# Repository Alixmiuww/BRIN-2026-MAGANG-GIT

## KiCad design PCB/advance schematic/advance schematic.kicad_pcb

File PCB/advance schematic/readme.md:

# ESP32 Controller — Schematic Documentation

## 1. Deskripsi Proyek

Proyek ini merupakan pengembangan rangkaian kontroler berbasis **ESP32-DevKitC-32E** yang menggunakan dua modul joystick analog, beberapa tombol kontrol, sensor GY-521 (MPU6050), LED RGB, serta rangkaian pemantauan tegangan baterai.

Rangkaian dirancang sebagai perangkat input untuk membaca pergerakan joystick, menerima perintah dari tombol, dan menyediakan data sensor untuk kebutuhan sistem kendali elektronik, seperti robot atau kendaraan berbasis mikrokontroler.

## 2. Fitur Utama

- **Dual Analog Joystick:** Membaca input sumbu X dan Y dari dua modul joystick.
- **Button Control:** Menyediakan tombol untuk kontrol drop, pickup, peningkatan kecepatan, penurunan kecepatan, dan pemilihan mode.
- **IMU Sensor:** Menggunakan GY-521 berbasis MPU6050 untuk membaca percepatan dan kecepatan sudut.
- **Battery Voltage Monitoring:** Menyediakan rangkaian pembagi tegangan untuk membaca tegangan baterai melalui ADC ESP32.
- **RGB LED Indicator:** Menyediakan indikator visual melalui LED RGB.
- **ESP32 Microcontroller:** Bertindak sebagai pusat pembacaan input dan pemrosesan data kontrol.

## 3. Komponen yang Digunakan

| Komponen | Fungsi |
|---|---|
| ESP32-DevKitC-32E | Mikrokontroler utama |
| 2× Joystick Module | Input analog sumbu X dan Y |
| 6× Push Button | Input perintah kontrol |
| GY-521 (MPU6050) | Sensor gerak berbasis IMU |
| LED RGB | Indikator status |
| Resistor 10 kΩ | Jaringan tombol dan pembagi tegangan |
| Resistor 100 kΩ | Pembagi tegangan pemantauan baterai |
| Konektor baterai | Input tegangan baterai |
| Sakelar | Pengendalian jalur rangkaian sesuai skematik |

## 4. Pemetaan Pin ESP32

### A. Input Joystick

| Sinyal | GPIO ESP32 |
|---|---:|
| JOY.VRx1 | GPIO 33 |
| JOY.VRy1 | GPIO 32 |
| JOY.VRx2 | GPIO 35 |
| JOY.VRy2 | GPIO 34 |

GPIO 32, 33, 34, dan 35 digunakan untuk membaca sinyal analog dari kedua joystick. GPIO 34 dan GPIO 35 merupakan pin input-only sehingga sesuai untuk pembacaan ADC.

### B. Tombol Kontrol

| Sinyal | GPIO ESP32 | Fungsi |
|---|---:|---|
| CONTROL.drop | GPIO 13 | Perintah drop |
| CONTROL.plck | GPIO 14 | Perintah pickup |
| CONTROL.up | GPIO 26 | Menaikkan kecepatan |
| CONTROL.down | GPIO 25 | Menurunkan kecepatan |
| SW.mode.joy1 | GPIO 18 | Pemilihan mode joystick |
| SW.mode.sensor | GPIO 19 | Pemilihan mode sensor |

**Catatan:** Pemetaan pin mengikuti label jaringan pada skematik. Pastikan konfigurasi pin pada program sesuai dengan hasil akhir desain PCB.

### C. Sensor GY-521 (MPU6050)

| Sinyal | Koneksi |
|---|---|
| VCC | +5 V sesuai skematik |
| GND | GND |
| SDA | Jalur I²C SDA |
| SCL | Jalur I²C SCL |
| AD0 | Tidak terhubung |
| INT | Tidak terhubung |
| XCL dan XDA | Tidak terhubung |

Jalur SDA dan SCL dihubungkan ke GPIO ESP32 yang ditentukan dalam konfigurasi perangkat lunak. Pin AD0 yang tidak terhubung umumnya membuat alamat I²C MPU6050 berada pada `0x68`, tetapi kondisi pin perlu dipastikan pada modul yang digunakan.

### D. LED RGB

LED RGB digunakan sebagai indikator status perangkat. Setiap kanal warna terhubung ke jalur GPIO melalui rangkaian pada skematik.

**Catatan:** Nomor GPIO untuk setiap kanal LED perlu dipastikan dari label net dan koneksi lengkap pada skematik sebelum diimplementasikan dalam kode.

### E. Pemantauan Tegangan Baterai

Rangkaian pemantauan tegangan menggunakan resistor pembagi tegangan untuk menyesuaikan tegangan baterai dengan rentang input ADC ESP32.

Nilai tegangan input dapat dihitung menggunakan:

`V_baterai = V_ADC × (R_atas + R_bawah) / R_bawah`

Rumus tersebut berlaku untuk pembagi tegangan standar, dengan `R_atas` terhubung dari baterai positif ke titik ADC dan `R_bawah` terhubung dari titik ADC ke GND.

**Penting:** Nilai resistor dan jalur pada skematik perlu diverifikasi. Pastikan tegangan yang masuk ke pin ADC tidak melebihi batas aman ESP32. Jika ingin mengukur tegangan baterai di atas rentang ADC, gunakan pembagi tegangan yang sesuai.

## 5. Prinsip Kerja Sistem

1. ESP32 dinyalakan melalui sumber daya yang sesuai.
2. Kedua joystick menghasilkan sinyal analog sesuai posisi sumbu X dan Y.
3. ESP32 membaca perubahan sinyal analog melalui ADC.
4. Tombol memberikan perintah digital untuk drop, pickup, pengaturan kecepatan, dan pemilihan mode.
5. Sensor MPU6050 menyediakan data percepatan dan kecepatan sudut melalui komunikasi I²C.
6. Rangkaian pembagi tegangan menyediakan sinyal yang mewakili tegangan baterai untuk dipantau ESP32.
7. Data input diproses oleh firmware untuk menentukan perintah kontrol dan status sistem.

## 6. Perangkat Lunak

Firmware dapat dikembangkan menggunakan Arduino IDE atau PlatformIO dengan framework Arduino.

Library yang dapat digunakan:
- `Arduino.h` — fungsi dasar ESP32.
- `Wire.h` — komunikasi I²C.
- Library MPU6050 yang kompatibel — pembacaan data IMU.

## 7. Catatan Desain dan Pengujian

Sebelum rangkaian diproduksi atau digunakan, lakukan pemeriksaan berikut:

- Verifikasi semua koneksi daya, GND, dan GPIO.
- Pastikan setiap tombol memiliki logika input yang sesuai dengan konfigurasi resistor.
- Periksa apakah resistor 10 kΩ pada jaringan tombol berfungsi sebagai pull-up atau pull-down sesuai kebutuhan.
- Pastikan tegangan keluaran joystick tidak melebihi batas ADC ESP32.
- Verifikasi konfigurasi pembagi tegangan baterai dan batas tegangan ADC.
- Pastikan LED RGB memiliki resistor pembatas arus yang sesuai untuk setiap kanal.
- Periksa alamat I²C MPU6050 dan jalur SDA/SCL menggunakan pemindaian I²C.
- Lakukan pemeriksaan ERC pada skematik dan DRC pada layout PCB sebelum fabrikasi.

## 8. Kesimpulan

Rangkaian ini dirancang sebagai kontroler berbasis ESP32 dengan input joystick analog, tombol digital, sensor IMU, indikator RGB, dan pemantauan tegangan baterai. Integrasi komponen tersebut memungkinkan ESP32 mengumpulkan berbagai input untuk diproses menjadi perintah kendali. Validasi koneksi daya, pemetaan GPIO, dan rangkaian ADC perlu dilakukan sebelum implementasi perangkat lunak dan pembuatan PCB.

## 9. Schematic Rancangan

## 10. PCB Rancangan

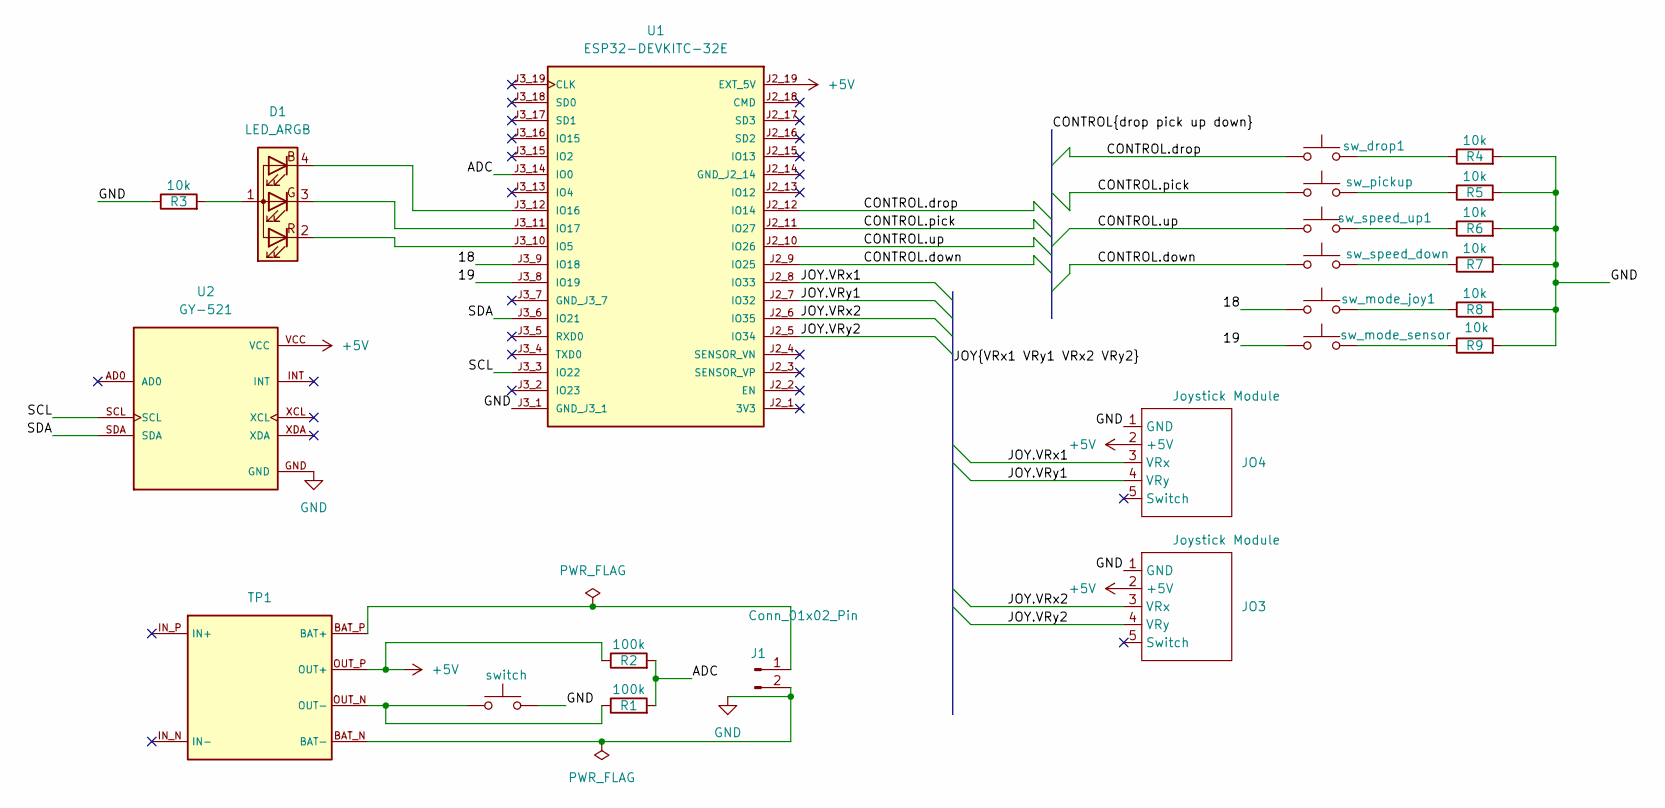
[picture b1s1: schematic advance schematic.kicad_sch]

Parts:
D1: LED_ARGB; LED_D5.0mm-4_RGB_Wide_Pins
J1: Conn_01x02_Pin; JST_EH_B2B-EH-A_1x02_P2.50mm_Vertical
JO3, JO4: Joystick Module; Module joystick
R1, R2: 100k; R_Axial_DIN0204_L3.6mm_D1.6mm_P1.90mm_Vertical
R3, R4, R5, R6, R7, R8, R9: 10k; R_Axial_DIN0204_L3.6mm_D1.6mm_P1.90mm_Vertical
SW2: sw_pickup; SW_PUSH_6mm
SW3: sw_speed_down; SW_PUSH_6mm
SW4: sw_mode_sensor; SW_PUSH_6mm
SW5: switch; SW_DIP_SPSTx01_Slide_6.7x4.1mm_W7.62mm_P2.54mm_LowProfile
TP1: MODULE_TP4056_MICRO-USB_CHARGER_-_1A
U1: ESP32-DEVKITC-32E; MODULE_ESP32-DEVKITC-32E; PARTREV 1.4
U2: GY-521; MODULE_GY-521; PARTREV NA
sw_drop1: SW_Push; SW_PUSH_6mm
sw_mode_joy1: SW_Push; SW_PUSH_6mm
sw_speed_up1: SW_Push; SW_PUSH_6mm

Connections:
+5V: JO3.2 (+5V), JO4.2 (+5V), R2.1, TP1.OUT_P (OUT+), U1.J2_19 (EXT_5V), U2.VCC
/18: U1.J3_9 (IO18), sw_mode_joy1.1
/19: SW4.1, U1.J3_8 (IO19)
/<NO NET>: D1.2 (RK), D1.4 (BK), U1.J3_10 (IO5), U1.J3_12 (IO16)
/ADC: R1.2, R2.2, U1.J3_14 (IO0)
/CONTROL.down: SW3.1, U1.J2_9 (IO25)
/CONTROL.drop: U1.J2_12 (IO14), sw_drop1.1
/CONTROL.pick: SW2.1, U1.J2_11 (IO27)
/CONTROL.up: U1.J2_10 (IO26), sw_speed_up1.1
/JOY.VRx1: JO4.3 (VRx), U1.J2_8 (IO33)
/JOY.VRx2: JO3.3 (VRx), U1.J2_6 (IO35)
/JOY.VRy1: JO4.4 (VRy), U1.J2_7 (IO32)
/JOY.VRy2: JO3.4 (VRy), U1.J2_5 (IO34)
/SCL: U1.J3_3 (IO22), U2.SCL
/SDA: U1.J3_6 (IO21), U2.SDA
GND: J1.2, JO3.1 (GND), JO4.1 (GND), R3.1, R4.2, R5.2, R6.2, R7.2, R8.2, R9.2, SW5.2, TP1.BAT_N (BAT-), U1.J3_1 (GND_J3_1), U2.GND
unnamed: D1.1 (A), R3.2
unnamed: D1.3 (GK), U1.J3_11 (IO17)
unnamed: J1.1, TP1.BAT_P (BAT+)
unnamed: R4.1, sw_drop1.2
unnamed: R5.1, SW2.2
unnamed: R6.1, sw_speed_up1.2
unnamed: R7.1, SW3.2
unnamed: R8.1, sw_mode_joy1.2
unnamed: R9.1, SW4.2
unnamed: R1.1, SW5.1, TP1.OUT_N (OUT-)

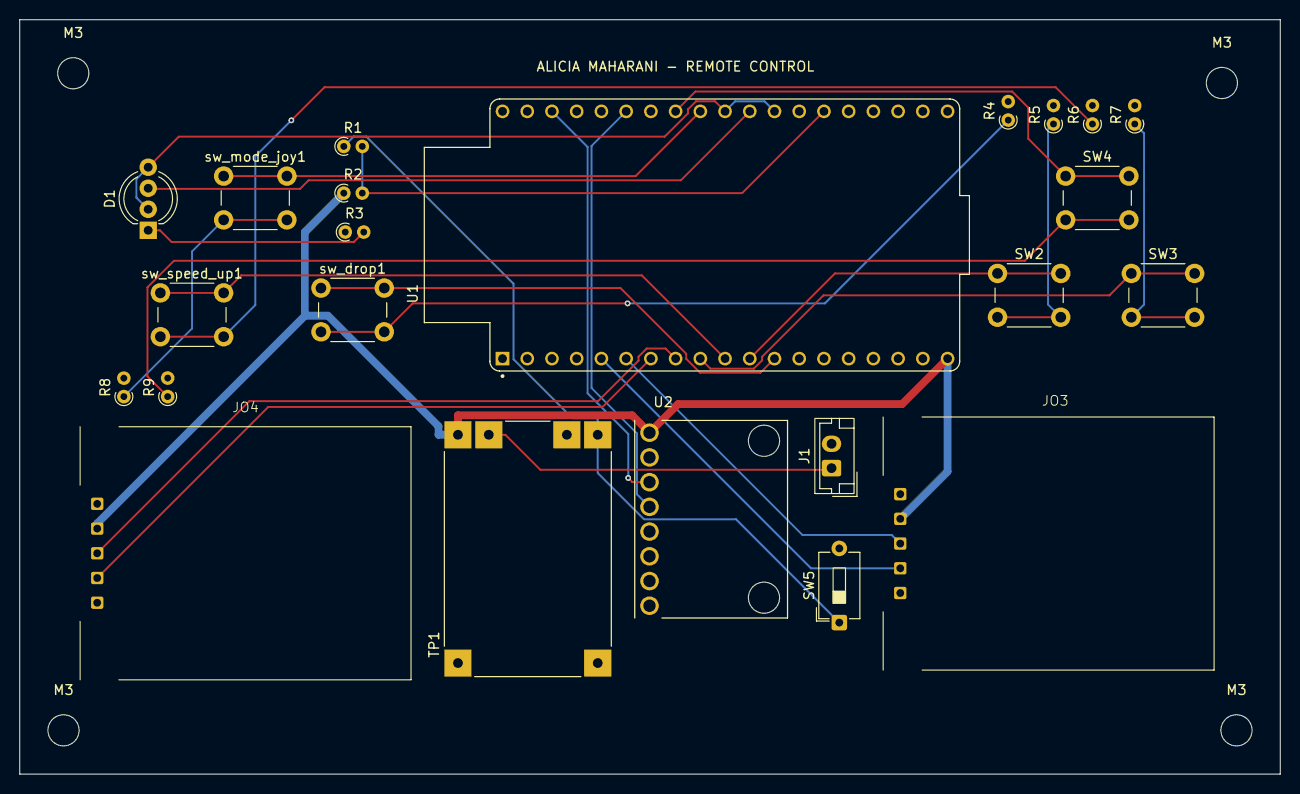
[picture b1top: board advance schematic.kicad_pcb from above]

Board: 2 copper layers, 129.5 x 77.5 mm, 27 parts (0 on the bottom side), 26 nets.

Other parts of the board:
M3, M3#2, M3#3, M3#4: MountingHole_3.2mm_M3

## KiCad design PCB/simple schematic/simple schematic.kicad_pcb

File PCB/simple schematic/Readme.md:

# Percobaan IC NE555 Timer

## 1. Deskripsi

Percobaan ini bertujuan untuk mempelajari penggunaan IC NE555 sebagai pembangkit sinyal pulsa (*pulse generator*). Rangkaian menggunakan konfigurasi astable atau osilator untuk menghasilkan sinyal keluaran secara periodik.

Sinyal keluaran dari pin 3 IC NE555 digunakan untuk mengendalikan LED sebagai indikator visual. Rangkaian menggunakan sumber tegangan 5 V, jaringan resistor, dan kapasitor untuk menentukan karakteristik sinyal yang dihasilkan.

## 2. Tujuan

- Memahami prinsip kerja IC NE555 Timer.
- Mempelajari konfigurasi rangkaian pembangkit pulsa.
- Memahami pengaruh resistor dan kapasitor terhadap frekuensi sinyal.
- Mengamati keluaran IC NE555 menggunakan LED.
- Memahami fungsi komponen pendukung pada rangkaian timer.

## 3. Alat dan Bahan

| No. | Komponen | Nilai / Tipe |
|---:|---|---|
| 1 | IC Timer | NE555P |
| 2 | Resistor R1 | 10 kΩ |
| 3 | Resistor R2 | 100 kΩ |
| 4 | Resistor R3 | 330 Ω |
| 5 | Kapasitor C1 | 10 µF |
| 6 | Kapasitor C2 | 100 nF |
| 7 | LED | 1 buah |
| 8 | Push button SW1 | 1 buah |
| 9 | Sumber tegangan | +5 V DC |
| 10 | Breadboard dan kabel jumper | Secukupnya |

## 4. Prinsip Kerja

IC NE555 dapat digunakan sebagai pembangkit sinyal pulsa dengan memanfaatkan proses pengisian dan pengosongan kapasitor.

Pada konfigurasi astable, tegangan kapasitor berubah secara periodik. Ketika tegangan kapasitor mencapai ambang tertentu, kondisi keluaran IC berubah sehingga menghasilkan sinyal pulsa berulang.

Sinyal keluaran tersebut dapat digunakan untuk mengendalikan LED sehingga perubahan kondisi keluaran dapat diamati secara visual.

## 5. Fungsi Komponen

| Komponen | Fungsi |
|---|---|
| NE555P | Menghasilkan sinyal pulsa |
| R1 (10 kΩ) | Bagian dari jaringan pengaturan dan pemicu rangkaian |
| R2 (100 kΩ) | Menentukan karakteristik pengisian dan pengosongan kapasitor sesuai konfigurasi |
| R3 (330 Ω) | Membatasi arus LED |
| C1 (10 µF) | Kapasitor timing yang memengaruhi periode sinyal |
| C2 (100 nF) | Kapasitor bypass atau decoupling untuk membantu menstabilkan suplai |
| SW1 | Tombol untuk mengubah kondisi rangkaian sesuai koneksinya |
| LED D1 | Indikator visual keluaran rangkaian |
| J1 | Konektor sumber daya +5 V dan GND |

## 6. Pin IC NE555

| Pin | Nama | Fungsi |
|---:|---|---|
| 1 | GND | Ground rangkaian |
| 2 | TRIG | Pemicu keluaran |
| 3 | OUT | Keluaran sinyal pulsa |
| 4 | RESET | Mengatur ulang atau menonaktifkan operasi IC ketika ditarik LOW |
| 5 | CONT | Mengatur tegangan referensi internal |
| 6 | THRES | Mendeteksi ambang tegangan kapasitor |
| 7 | DISCH | Jalur pengosongan kapasitor |
| 8 | VCC | Tegangan suplai positif |

## 7. Langkah Pengujian

1. Rakit rangkaian sesuai dengan skematik.
2. Pastikan seluruh koneksi IC NE555 sesuai dengan nomor pin.
3. Hubungkan sumber tegangan +5 V dan GND.
4. Amati kondisi LED setelah rangkaian diberi daya.
5. Tekan push button dan amati perubahan kondisi rangkaian.
6. Jika tersedia osiloskop, ukur sinyal keluaran pada pin 3 untuk mengamati bentuk gelombang, frekuensi, dan duty cycle.
7. Catat hasil pengamatan dan bandingkan dengan karakteristik rangkaian yang direncanakan.

## 8. Hasil yang Diharapkan

- IC NE555 bekerja sesuai konfigurasi rangkaiannya.
- Sinyal keluaran dapat diamati pada pin 3.
- LED menunjukkan perubahan kondisi sesuai sinyal keluaran.
- Pengukuran menggunakan osiloskop memperlihatkan bentuk gelombang keluaran yang sesuai dengan konfigurasi rangkaian.

## 9. Kesimpulan

Percobaan ini memperkenalkan penggunaan IC NE555 sebagai pembangkit sinyal pulsa. Resistor dan kapasitor berperan dalam menentukan karakteristik waktu rangkaian, sedangkan LED digunakan sebagai indikator keluaran. Pengukuran menggunakan osiloskop dapat membantu mengetahui frekuensi, periode, dan duty cycle sinyal secara lebih akurat.

## 10. Schematic Rangkaian 

## 11. PCB Rangkaian

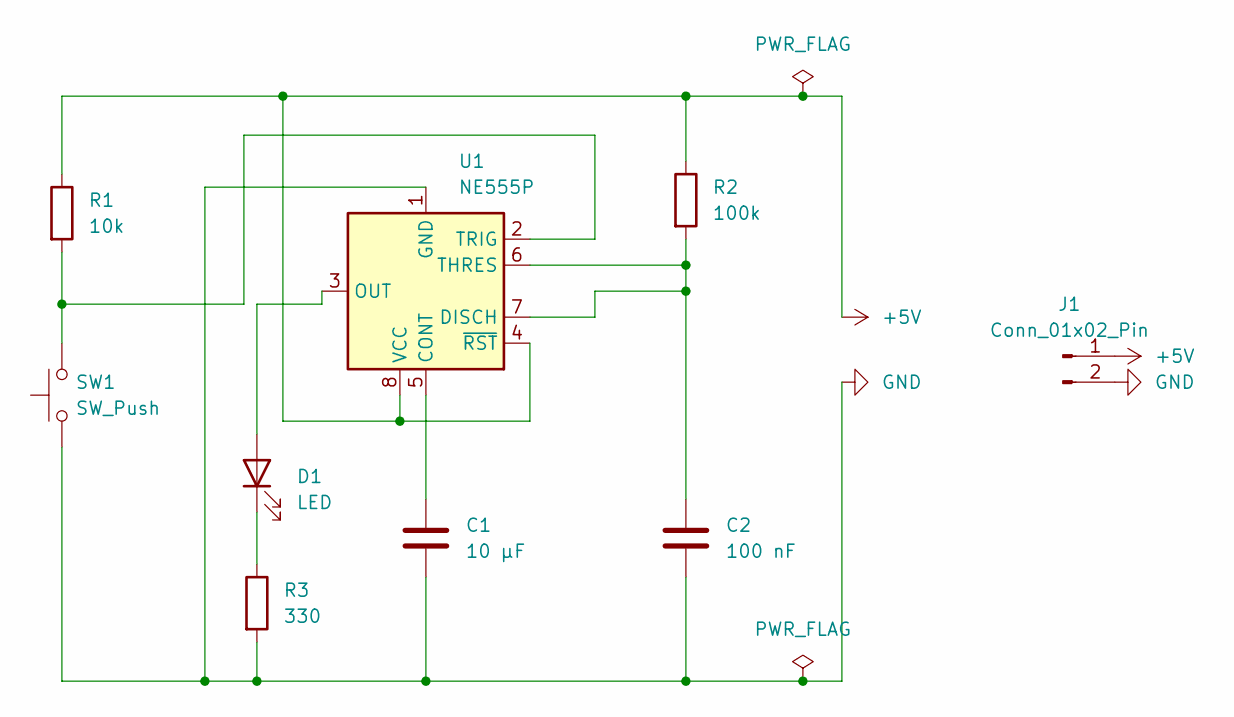
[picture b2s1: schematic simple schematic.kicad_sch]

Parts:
C1: 10 µF; CP_Radial_D6.3mm_P2.50mm
C2: 100 nF; C_Disc_D4.3mm_W1.9mm_P5.00mm
D1: LED; LED_D3.0mm
J1: Conn_01x02_Pin; JST_EH_B2B-EH-A_1x02_P2.50mm_Vertical
R1: 10k; R_Axial_DIN0204_L3.6mm_D1.6mm_P7.62mm_Horizontal
R2: 100k; R_Axial_DIN0204_L3.6mm_D1.6mm_P7.62mm_Horizontal
R3: 330; R_Axial_DIN0204_L3.6mm_D1.6mm_P7.62mm_Horizontal
SW1: SW_Push; SW_PUSH_6mm
U1: NE555P; DIP-8_W7.62mm

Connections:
+5V: J1.1, R1.1, R2.1, U1.4 (~RST), U1.8 (VCC)
GND: C1.2, C2.2, J1.2, R3.2, SW1.1, U1.1 (GND)
unnamed: D1.2 (A), U1.3 (OUT)
unnamed: D1.1 (K), R3.1
unnamed: C1.1, U1.5 (CONT)
unnamed: C2.1, R2.2, U1.6 (THRES), U1.7 (DISCH)
unnamed: R1.2, SW1.2, U1.2 (TRIG)

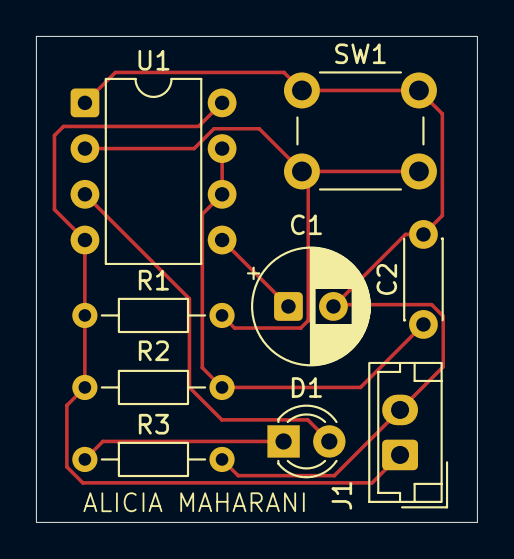
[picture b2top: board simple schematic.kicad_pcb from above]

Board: 2 copper layers, 24.5 x 27.0 mm, 9 parts (0 on the bottom side), 7 nets.
